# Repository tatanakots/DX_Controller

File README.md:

# DX Controller

一个基于MaiPico再开发的适用于某品牌洗衣机的控制器。

### 项目特点

1. 由于~~买错配件~~新版比较好看，所以主控替换为搭载RP2350的树莓派Pico 2。
1. 更改了部分按键映射，以匹配丝印的键位。
1. 增加了TDX Pro，可以制作大台。（还在测试中）

### 串口配置

以下配置说明均为默认 `config_common.json` 中的配置，如果你修改过 `config_common.json` 中的配置，请根据你的配置进行修改。

| 串口名称 | 1P端口号 | 2P端口号 |
| ------- | -------- | -------- |
| TDX Controller Command Line Port | 不重复的随意端口号 | 不重复的随意端口号 |
| TDX Controller Touch Port | COM3 | COM4 |
| TDX Controller LED Port | COM21 | COM23 |
| TDX Controller AIME Port | COM1 | 仅需设置一个即可，无法同时使用两个读卡器 |

### 命令行使用说明

可以通过[这个链接](https://googlechromelabs.github.io/serial-terminal/)打开命令行工具，选择 `TDX Controller Command Line Port` 连接后按提示使用即可。

### 关于授权

由于固件修改自[MaiPico](https://github.com/whowechina/mai_pico)，而该项目中对固件指定了使用[GPL 3.0](/firmware/LICENSE)协议，所以固件部分按照[GPL 3.0](/firmware/LICENSE)协议开源，其余我自己创建和修改的部分则按照[MIT](/LICENSE)协议开源。

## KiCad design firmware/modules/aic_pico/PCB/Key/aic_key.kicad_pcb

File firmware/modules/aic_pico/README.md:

# AIC Pico, AIC Key and AIC Touch
  **AIME Reader & Bandai Namco Reader & Cardio Emulator**

[点这里可以切换到中文版](README_CN.md)

**Features:**
* It's small, smallest as far as I know.
* Many variants
  * AIC Pico (PN532)
  * AIC Pico (PN5180, no housing)
  * AIC Key PN532/PN5180
  * AIC Touch PN532/PN5180
  * AIC Pico Lib (see notes 1 below)
* Easy to make.
* Sega AIME I/O, Bandai Namco I/O and Spicetools CardIO emulation.
* Automatic detection of I/O protocols above.
* Command line for configurations.
* Supported card:
  * FeliCa (Amusement IC)
  * ISO/IEC 14443 Type A (BanaPassport, Mifare, Amiibo, some IC tags, some ID tags, etc.)
  * ISO/IEC 15693 (Old E-Amusement cards), only with PN5180 (see notes 2 below)
* Emulates virtual AIC from any Mifare cards (not for Bandai Namco I/O).
* All source files open.

**Notes:**
1. So one can integrate "AIC Pico" into other Raspberry Pi Pico based projects. See my Chu Pico project and see how it works.  

2. PN532 supports only 14443A (Mifare) and FeliCa cards, while PN5180 also supports 15693 cards (old e-Amusement cards).

## Thanks
Thanks to many respectful guys/companies who made their tools or materials free or open source (KiCad, OnShape, InkScape, Fritzing, Raspberry things), ChatGPT and GitHub Copilot helped a lot as well.

And thanks to community developers and projects that helped me a lot:
* CrazyRedMachine (https://github.com/CrazyRedMachine) for the Spicetools Card IO part;
* Sucareto's AIME Reader (https://github.com/Sucareto/Arduino-Aime-Reader) for the AIME protocol part;
* Bottersnike (https://gitea.tendokyu.moe/Bottersnike, https://sega.bsnk.me/) for AIME and FeliCa knowledge;
* .NET nanoFramework (https://github.com/nanoframework) for the PN5180 part;
* Gyt4 (https://github.com/gyt4/) for Bandai Namco card reader I/O；
* Bananatools (https://gitea.tendokyu.moe/Hay1tsme/bananatools) for Bandai Namco card reader I/O；
* chujohiroto (https://github.com/chujohiroto/Raspberry-RCS620S/blob/master/rcs620s.py), as indirect reference for the Bandai Namco card reader I/O；

## Warning
This project:  
* Heavily depends on 3D printing, a Bambu AMS system helps a lot.
* Requires skills to solder tiny components and wires.

## My Other Projects
You can check out my other cool projects.

* Popn Pico: https://github.com/whowechina/popn_pico
* IIDX Pico: https://github.com/whowechina/iidx_pico
* IIDX Teeny: https://github.com/whowechina/iidx_teeny
* Chu Pico: https://github.com/whowechina/chu_pico
* Mai Pico: https://github.com/whowechina/mai_pico
* Diva Pico: https://github.com/whowechina/diva_pico
* AIC Pico: https://github.com/whowechina/aic_pico
* Groove Pico: https://github.com/whowechina/groove_pico
* Geki Pico: https://github.com/whowechina/geki_pico
* Musec Pico: https://github.com/whowechina/musec_pico
* Ju Pico: https://github.com/whowechina/ju_pico

## **Disclaimer** ##
I made this project in my personal time with no financial benefit or sponsorship. I will continue to improve the project. I have done my best to ensure that everything is accurate and functional, there's always a chance that mistakes may occur. I cannot be held responsible for any loss of your time or money that may result from using this open source project. Thank you for your understanding.

## About the License
It's CC-NC. So DIY for yourself and for your friend, don't make money from it. And plagiarism that doesn’t even dare to mention the original author is not acceptable. Plase note that pooling orders and group buying for raw materials is acceptable. Selling off any leftover components without profit is also acceptable.

If you're interested in buying from me or for commercial use, please contact me (Discord, QQ group, Wechat group or leave your contact in issue section).

## My Discord Invitation
https://discord.gg/M8f2PPQFEA

## List of Building Choices
- [AIC Pico PN532](#Building-AIC-Pico-PN532)
- [AIC Pico PN5180](#Building-AIC-Pico-PN5180)
- [AIC Key](#Building-AIC-Key)
- [AIC Touch](#Building-AIC-Touch)

## Building AIC Pico PN532
Seriously, this is the easiest one among all my Pico series projects.
### Components
* 1x Rasberry Pi Pico or Pico W (clones work too).  
  https://www.raspberrypi.com/products/raspberry-pi-pico
* 1x PN532 Module (the Red Square board version, cheap clones work too).  
  https://www.elechouse.com/product/pn532-nfc-rfid-module-v4/
* Some thin wires.
* Thin WS2812B LED strip.
* 4x M2*8mm screws.

### 3D Prints
* **aic_pico_bottom.stl**  
  The bottom part.

For the top part, choose one that fits your need.
* **aic_pico_top.stl**  
  Regular top part.
* **aic_pico_top_ams.3mf**  
  Regular top part, multi-color printing.
* **aic_pico_top_tall.stl**  
  Taller top part, so a thicker LED strip can fit.
* **aic_pico_top_tall_ams.3mf**  
  Taller top part, multi-color printing.

Top parts should be printed upside-down.

### Wiring

### Assembly
I'll let these images do the talk.

#### Notes
* The firmware supports up to 64 LEDs on the WS2812B LED strip. I personally used 3 as shown in main title image. But you can have different LED number, as long as they fit within the housing.
* LED might be excessively bright even at low settings, consider covering it with some filter tape.
* The mode switch on PN532 must be in "I2C" mode, picture below shows the correct settings.  

## Building AIC Pico PN5180
If you opt for the PN5180 NFC module, note that the housing design is up to you. Ensure it fits your design or you can use it without a case. Be prepared to solder more wires compared to the PN532 version.

### Wiring

Note: WS2812B LED Strip wiring is the same as the PN532 version.

## Building AIC Key
AIC Key is a variation of the AIC Pico - a keypad is integrated. Much more difficult to build than the "AIC Pico" as it has many tiny components to solder.

### Components
* 1x Rasberry Pi Pico or Pico W (clones work too).  
  https://www.raspberrypi.com/products/raspberry-pi-pico

* For NFC modules, choose one of the following options:
  * 1x PN532 Module (the red square board version, cheap clones work too).  
    https://www.elechouse.com/product/pn532-nfc-rfid-module-v4/
  * 1x PN5180 Module (the blue rectangle version, cheap clones work too). PN5180 supports ISO/IEC 15693 (old e-amusement cards).  

* For LEDs, you also have 2 options:
  * Option 1: 6x side-light WS2812B 1204 LEDs (D1 to D6) and a 10ohm 0603 resistor (R1), GREEN mark in the assemble image. (available for both AIC Key and AIC Touch)
  * Option 2: 6x regular single-color 0603 LEDs (D7 to D12) and 6x 100ohm 0603 resistors (R2 to R7), PURPLE mark in the assemble image. (available for AIC Key only)

* C1, C2, C3, 0603 10uF capacitors, they contribute to a more stable power supply.

* For switches, you still have 2 option:
  * Option 1: 12x ALPS SKRRAAE010 low-profile TACT switch.  
    https://www.mouser.com/ProductDetail/Alps-Alpine/SKRRAAE010?qs=m0BA540hBPeKhAe3239t1w%3D%3D
  * Option 2: 12x Panasonic EVQP1K05M 6mm square tactile switch.  
    https://www3.panasonic.biz/ac/e/dl/catalog/index.jsp?series_cd=3473&part_no=EVQP1K05M

* 1x Right angle 2.54mm pitch header, 4P for PN532, 13P for PN5180.  

* 1x Stickers of numbers. You can find some customize sticker service, or you can find some existing stickers. I found this Bonito crystal 3D stickers super helpful for this project.  

* PCB, visit JLCPCB (https://jlcpcb.com/) and place an order there. Leave everything default, 1.6mm thickness, whatever color you like. The PCB gerber file is "Production/PCB/aic_key_v*.zip".  

### 3D Prints
* **aic_key_bottom.stl**  
  Bottom part.
* **aic_key_top_surface.stl**  
  Top part for Alps surface switches.
* **aic_key_top_surface_ams.3mf**  
  Top part for Alps surface switches, multi-color printing.
* **aic_key_top_tact.stl.stl**  
  Top part for Panasonic tact switches.
* **aic_key_top_tact_ams.3mf**  
  Top part for Panasonic tact switches, multi-color printing.

Top parts should be printed upside-down.

### Assembly
Again I'll let these images do the talk. Remember to upload the firmware onto Raspberry Pi Pico before assemble.
Please note, the latest PCB is compatible with both PN532 and PN5180, and you can solder according to your needs. The photos below are based on an earlier version of the PCB and may not correspond exactly, but I believe you will be able to understand.

#### General Part

#### PN532 Version
Remember set to I2C mode first.

**CAUTION:**
- There's a possibility that the antenna on the PN532 PCB may come into contact with the USB connector and cause RF problem. To prevent this, you can apply some insulating tape.

- Due to manufacturing errors, your PN532 module may not fit perfectly into the housing. If necessary, you can gently trim the edges of the PN532 module for a better fit.

#### PN5180 Version
You need to cut off the original antenna and use the one in our PCB.

#### Final Assembly
You may use some instant adhesive to fix stickers.

## Building AIC Touch
AIC Touch, another variant of AIC Pico, comes with an integrated touchscreen. However, its tiny FPC/FFC connector significantly increases the soldering and assembly difficulty.

### Components
* For the Raspberry Pi Pico, NFC module, 6x WS2812B 1204 LEDs and the R1 resistor part, follow the guide for AIC Key.
* C1, C2, C3, 0603 0.1uF capacitors, they contribute to a more stable power supply.
* R2, R3, pull-up resistors for the I2C bus, 0603 1Kohm ~ 4.7Kohm.
* 1.69 inch 240x280 LCD touchscreen (ST7789 + CST816). Several vendors are making this model, as long as one has the exact same looking, it will be fine. It looks like this.

* The FPC/FFC flip cover connector for the touchscreen. 18P, 0.5mm Pitch, 1.0H (1mm height), front flip (flip cover at cable side), bottom contact. It looks like this:

* PCB file "aic_touch_v*.zip".  

### 3D Prints
* **aic_touch_bottom.stl**  
  Bottom part.
* **aic_touch_top.stl**  
  Top part.
* **aic_touch_top.3mf** or **aic_touch_top_ams.3mf**  
  Top part for multi-color printing. The latter is for Bambu Studio with AMS system. Filament 1 is black, Filament 2 is clear transparent.

Top parts should be printed upside-down.

To achieve the best aesthetic results, I recommend using the combination of clear PLA and black PLA. For the top part, make the first 2 layers of the sub-object "Top" black, and all others clear.    

### Assembly
For most of the part, just follow the guide of AIC key.

* The touchscreen will block PN532's RF signal so we need to offload the antenna to AIC Touch's PCB just like what we do in PN5180 version.
  * To build PN5180 version, short the "PN532 ANT" (green mark in the picture). To build PN532 version, short the "PN5180 ANT" (red mark in the picture).     
    
  * Not like the PN5180, the PN532 has 3 pins - it has a center tap. Here's how you offload the antenna from the PN532. Cut (with small knife or chisel) the original 2 traces of the antenna (green marks in the picture) and connect 3 "PN532 ANT" pins to the PN532 module.    

* Soldering the 18P-0.5mm-1.0H FPC/FFC connector can be challenging. Here are some tips to make the process easier:
  * Use a small, sharp iron tip, the smaller the better.
  * Set your soldering iron to a lower temperature, below 280 degrees Celsius.
  * Apply a generous amount of high-quality solder flux to keep the pins "wet" during soldering.
  * Use thin low-temperature solder wire (for example, diameter of 0.3mm).
  * Start by soldering the mounting pins on both sides for proper alignment, then proceed with the 18 main pins.
  * Don't feed solder wire directly onto the main pins.
  * When soldering main pins, only apply a very small amount of solder to the iron tip.
  * If you apply too much solder, a solder wick can be used effectively to remove the excess.

* Remember to put 1mm-thick soft pads to support the touchscreen. You can use 1mm 3M VHB double-sided tape, but do NOT remove the red film liner (don't let the tape stick to the touchscreen).

* Done!

## Firmware
* UF2 file is in `Production\Firmware` folder.
* There're several ways to boot into firmware update mode:
  * For the new build, hold the BOOTSEL button while connect the USB to a PC, there will be a disk named "RPI-RP2" showed up. Drag the UF2 firmware binary file into it. That's it.
  * If there's already a working firmware, you can use "update" command in command line to update the firmware in the future, so you don't need to open the housing.
  * If there's already a working firmware later than 2023-12-02, you can also press "00" key and "·" key (or directly ground the GPIO10 and the GPIO11) at the same time when plug in the USB cable, it will boot into firmware update mode.
* One USB serial port is for command line. You can use this Web Serial Terminal to connect to it. (Note: "?" is for help)  
  https://googlechromelabs.github.io/serial-terminal/
* The other serial port is for reader protocol, currently SEGA AIME and Bandai Namco are supported.
* Spicetools cardio (Card I/O) HID is always enabled unless a reader protocol is active;
* If your PN5180 module has an issue with Mifare (Such as AIME and Bana Passport) reading, you can try enable the PN5180 TX tweak by "pn5180_tweak on" command.
* Some command line commands:
  * "light \<rgb|led|both|off\>" to turn on or off the LEDs.
  * "level <0..255> <0..255>" to adjust the brightness.
  * "nfc" manually to detect cards.
  * "update" reboot into firmware update mode.
* Given my limited hobby time, the firmware may not be fully tested. Please report any anomalies.

## Card ID Logic
To support many different NFC cards and tags, card IDs are transformed following these rules.
### AIME
* 15693 => 0x01 + last 7 bytes of UID
* MIFARE (4-byte UID) => 0x01 + 0x01 + UID + first 2 bytes of the UID
* MIFARE (7-byte UID) => 0x01 + UID
* FeliCa => Original IDm
### CardIO
* 15693 => original UID
* MIFARE (4-byte UID) => 0xE0 + 0x04 + UID + first 2 bytes of the UID
* MIFARE (7-byte UID) => 0xE0 + UID
* FeliCa => Original IDm
### Bandai Namco
* MIFARE (4-byte UID) => UID
* FeliCa => Original IDm

## 3D Model Source File (Onshape)
https://cad.onshape.com/documents/ca5497f91b2962105335e822/w/7b88022e98c02c60ad0c44a7/e/c3476efd13c08f807f3773fe?configuration=List_6ARRO0azcgmmHg%3D__&renderMode=1&rightPanel=configPanel&uiState=6558cabf9b380560ca5b554e

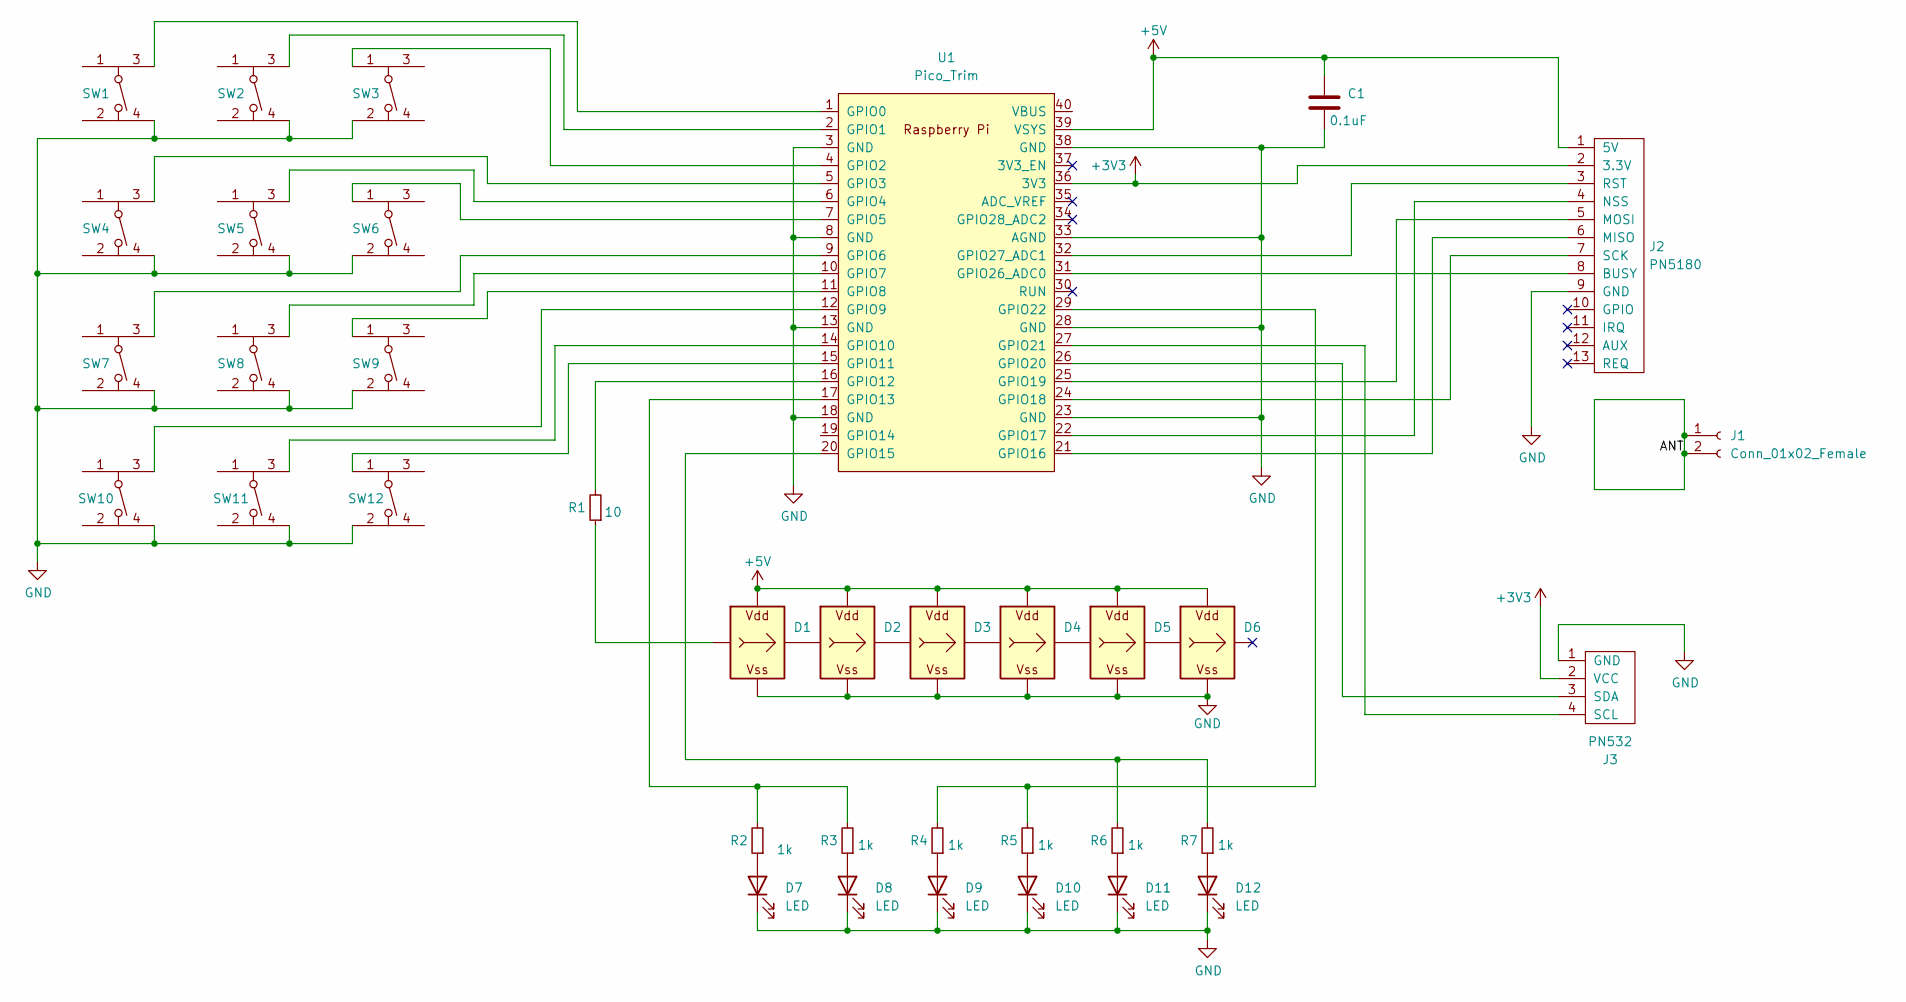
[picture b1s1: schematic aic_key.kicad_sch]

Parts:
C1: 0.1uF; C_0603_1608Metric
D1, D2, D3, D4, D5, D6: WS2812B_Unified; WS2812B-1204
D7, D8, D9, D10, D11, D12: LED; LED_0603_1608Metric_Pad1.05x0.95mm_HandSolder
J1: Conn_01x02_Female; ANT_2P
J2: PN5180; pn5180_conn
J3: PN532; pn532_conn
R1: 10; R_0603_1608Metric; LCSC C23186
R2, R3, R4, R5, R6, R7: 1k; R_0603_1608Metric; LCSC C23186
SW1, SW2, SW3, SW4, SW5, SW6, SW7, SW8, SW9, SW10, SW11, SW12: SKRR_4pin; SKRR
U1: Pico_Trim; RPi_Pico_SMD_No_USB

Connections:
+3V3: J2.2 (3.3V), J3.2 (VCC), U1.36 (3V3)
+5V: C1.1, D1.V (VDD), D2.V (VDD), D3.V (VDD), D4.V (VDD), D5.V (VDD), D6.V (VDD), J2.1 (5V), U1.39 (VSYS)
/ANT: J1.1, J1.2
GND: C1.2, D1.G (VSS), D2.G (VSS), D3.G (VSS), D4.G (VSS), D5.G (VSS), D6.G (VSS), D7.1 (K), D8.1 (K), D9.1 (K), D10.1 (K), D11.1 (K), D12.1 (K), J2.9 (GND), J3.1 (GND), SW1.4, SW2.4, SW3.2, SW4.4, SW5.4, SW6.2, SW7.4, SW8.4, SW9.2, SW10.4, SW11.4, SW12.2, U1.3 (GND), U1.8 (GND), U1.13 (GND), U1.18 (GND), U1.23 (GND), U1.28 (GND), U1.33 (AGND), U1.38 (GND)
unnamed: D1.I (In), R1.1
unnamed: D1.O (Out), D2.I (In)
unnamed: D2.O (Out), D3.I (In)
unnamed: D3.O (Out), D4.I (In)
unnamed: D4.O (Out), D5.I (In)
unnamed: D5.O (Out), D6.I (In)
unnamed: D7.2 (A), R2.1
unnamed: D8.2 (A), R3.1
unnamed: D9.2 (A), R4.1
unnamed: D10.2 (A), R5.1
unnamed: D11.2 (A), R6.1
unnamed: D12.2 (A), R7.1
unnamed: J2.8 (BUSY), U1.31 (GPIO26_ADC0)
unnamed: J2.6 (MISO), U1.21 (GPIO16)
unnamed: J2.5 (MOSI), U1.25 (GPIO19)
unnamed: J2.4 (NSS), U1.22 (GPIO17)
unnamed: J2.3 (RST), U1.32 (GPIO27_ADC1)
unnamed: J2.7 (SCK), U1.24 (GPIO18)
unnamed: J3.4 (SCL), U1.27 (GPIO21)
unnamed: J3.3 (SDA), U1.26 (GPIO20)
unnamed: SW1.3, U1.1 (GPIO0)
unnamed: SW2.3, U1.2 (GPIO1)
unnamed: SW3.1, U1.4 (GPIO2)
unnamed: SW4.3, U1.5 (GPIO3)
unnamed: SW5.3, U1.6 (GPIO4)
unnamed: SW6.1, U1.7 (GPIO5)
unnamed: SW7.3, U1.9 (GPIO6)
unnamed: SW8.3, U1.10 (GPIO7)
unnamed: SW9.1, U1.11 (GPIO8)
unnamed: SW10.3, U1.12 (GPIO9)
unnamed: SW11.3, U1.14 (GPIO10)
unnamed: SW12.1, U1.15 (GPIO11)
unnamed: R1.2, U1.16 (GPIO12)
unnamed: R2.2, R3.2, U1.17 (GPIO13)
unnamed: R6.2, R7.2, U1.20 (GPIO15)
unnamed: R4.2, R5.2, U1.29 (GPIO22)

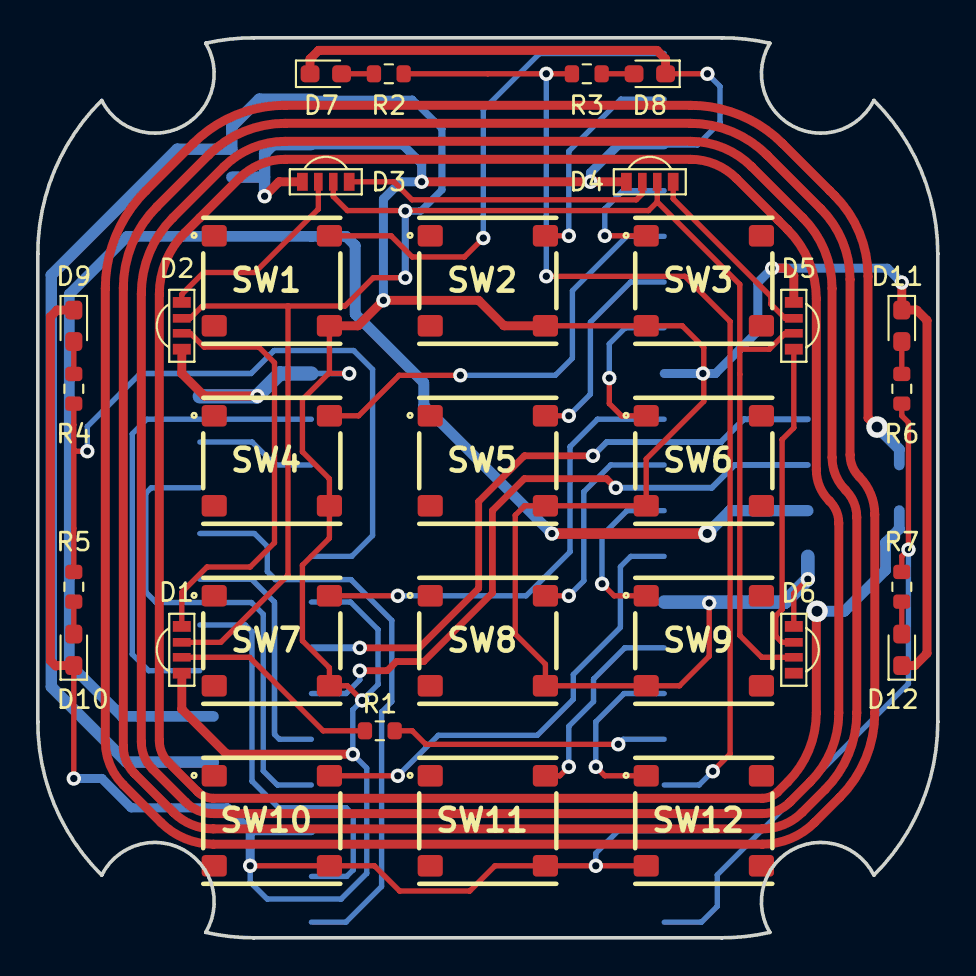
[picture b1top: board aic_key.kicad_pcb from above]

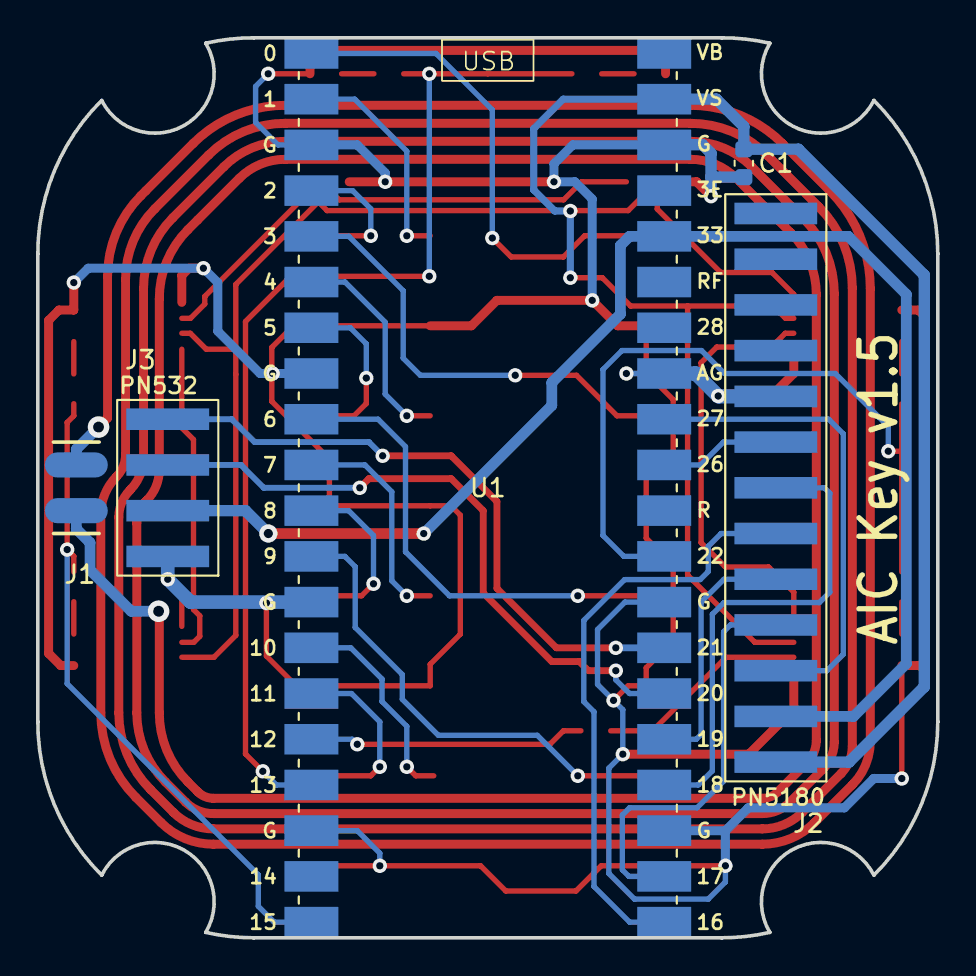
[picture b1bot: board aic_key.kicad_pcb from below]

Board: 2 copper layers, 50.0 x 50.0 mm, 36 parts (5 on the bottom side), 40 nets.

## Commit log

2025-02-27 chore: init commit
2025-02-27 docs: fix strikethrough syntax issue in README
2025-03-15 hardware: change the touch subboard hardware design to remove the i2c relay.
2025-03-16 hardware: change the main board hardware design to remove the i2c relay.
2025-03-16 cli: auto build firmware
2025-03-16 cli: fix bugs
2025-03-16 cli: Change the trigger condition
2025-03-16 cli: fix bug
2025-03-16 cli: try to get the artifact
2025-03-16 cli: debugging
2025-03-16 cli: Trying to fix artifact not existing
2025-03-25 ci: build pico 1 firmware too
2025-03-25 ci: fix bugs
2025-03-25 ci: fix pico 1 build error
2025-03-25 ci: fix Summarize problem
2025-03-31 chore: fix typos
